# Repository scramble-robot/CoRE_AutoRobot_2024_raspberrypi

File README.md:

# SDカード

1. Raspberry Pi ImagerでRaspberry Pi OS Lite (64-bit,**bullseye**)をMicro SDに書き込む。Imagerの設定でユーザ名**pi**とパスワードを予め設定すること。
2. Micro SDに作成された"bootfs"ドライブ直下に`ssh`という名前のファイルを配置してSSHを有効化する。
3. OS起動後、本レポジトリの`ros2_ws`及び`service`ディレクトリをホームディレクトリ(`/home/pi/`)にコピーする。

# C620とのCAN通信

MCP2515を用いてSPIからCANを制御

- (参考) [RaspberryPiとMCP2515でCAN通信をやってみる](https://qiita.com/h-kiyo/items/d8583af13768ad67bcd0)

## ハードウェア
1Mbpsの通信を行うために、水晶振動子を**16MHz**に交換すること

## CAN-BUSの有効化
1. `/boot/config.txt`を編集してSPIとMCP2515を有効化する
    ```bash
    sudo vi /boot/config.txt
    ```

    ```
    # Uncomment some or all of these to enable the optional hardware interfaces
    #dtparam=i2c_arm=on
    #dtparam=i2s=on
    dtparam=spi=on

    # MCP2515
    dtparam=spi=on
    dtoverlay=mcp2515-can0,oscillator=16000000,interrupt=25
    dtoverlay=spi-bcm2835-overlay
    ```

2. 初期化できているか確認
    ```
    dmesg | grep mcp251x
    ```

## can-utilsのインストール
```bash
sudo apt install can-utils
```

## 通信テスト

1Mbpsでlink up

```bash
sudo ip link set can0 type can bitrate 1000000 loopback off
sudo ip link set can0 up
sudo ifconfig can0 txqueuelen 1000
sudo ifconfig
```

### 受信テスト
```bash
candump can0
```

C620と通信できていると、以下のようなデータが受信される。
```text
  can0  201   [8]  0E 16 00 00 FF FD 21 00
  can0  201   [8]  0E 16 00 00 FF FD 21 00
  can0  201   [8]  0E 16 00 00 FF BE 21 00
  can0  201   [8]  0E 16 00 00 FF FD 21 00
  can0  201   [8]  0E 16 00 00 00 3D 21 00
```

### 送信
モータ回るはず
```bash
cansend can0 200#0200000000000000
```

## systemdによるCANバスの自動有効化

1. systemdの設定
    ```bash
    sudo vi /etc/systemd/network/80-can.network
    ```

    ```text
    [Match]
    Name=can*

    [CAN]
    BitRate=1000000
    ```

    設定後、以下コマンド実行
    ```bash
    sudo systemctl enable systemd-networkd
    sudo systemctl start systemd-networkd
    ```

2. txqueuelenの自動設定
    ```bash
    sudo vi /etc/udev/rules.d/71-can-txqueuelen.rules
    ```

    ```
    SUBSYSTEM=="net", ACTION=="add|change", KERNEL=="can*", ATTR{tx_queue_len}="1000"
    ```

3. 再起動後、`ifconfig`でlink upしていることを確認

    ```
    can0: flags=193<UP,RUNNING,NOARP>  mtu 16
            unspec 00-00-00-00-00-00-00-00-00-00-00-00-00-00-00-00  txqueuelen 1000  (UNSPEC)
            RX packets 0  bytes 0 (0.0 B)
            RX errors 0  dropped 0  overruns 0  frame 0
            TX packets 0  bytes 0 (0.0 B)
            TX errors 0  dropped 0 overruns 0  carrier 0  collisions 0
    ```

## Pythonからの制御

```bash
pip install python-can
```

```python
import can
import struct
import time

bus = can.interface.Bus(bustype="socketcan", channel="can0", bitrate=1000000)

def set_current(bus, currents):
    d = [0]*8
    raw_array = [0]*4
    for i in range(4):
        v = int(round(currents[i]/20 * 16384))
        v = min(v, 16384)
        v = max(v, -16384)
        raw_array[i] = v
    b = struct.pack('>4h', *raw_array)
    msg = can.Message(arbitration_id=0x200, is_extended_id=False, data=b)
    bus.send(msg)

def parse_c620_data(msg: can.Message):
    data = struct.unpack('>hhhbb', msg.data)
    degree = data[0]/ 8192 * 360
    rpm = data[1]
    current = data[2]/16384*20
    temperature = data[3]
    return degree, rpm, current, temperature

def can_receive_callback(msg: can.Message) -> None:
    #print(msg)
    if msg.arbitration_id >= 0x201 and msg.arbitration_id < 0x204:
        degree, rpm, current, temperature = parse_c620_data(msg)
        print(f'{degree:.1f}\t{rpm:+5d}\t{current:.1f}\t{temperature:2d}')

notifier = can.Notifier(bus, [can_receive_callback])

set_current(bus, [1, -1, 0, 0])
time.sleep(1)

set_current(bus, [-1, 1, 0, 0])
time.sleep(1)

for i in range(4):
    set_current(bus, [0, 0, 0, 0])
    time.sleep(1)

notifier.stop()
bus.shutdown()
```

# サーボモータ
## ハードウェア
- 信号線はGPIO17に接続
- サーボモータの5Vは外部電源から取ること

## requirements
```bash
sudo apt install -y pigpio python3-pigpio
sudo pigpiod
sudo systemctl enable pigpiod
```

## 動作確認

```python
import pigpio

output_pin = 12 # 12 or 13

def setServoDegree(pi, output_pin, degree):
    min_width = 500
    max_width = 2500
    deg_range = 270
    output = degree / deg_range
    output *= max_width - min_width
    output += min_width
    output = int(output)
    pi.set_servo_pulsewidth(output_pin, output)

pi = pigpio.pi()
pi.set_mode(output_pin, pigpio.OUTPUT)
pi.set_servo_pulsewidth(output_pin, 0)

while True:
    print("input Duty Cyle (0 - 270)")
    degree = float(input())
    setServoDegree(pi, output_pin, degree)
```

# ROS2のインストール

Raspbian OS用の、[非公式のdebパッケージ](https://github.com/Ar-Ray-code/rpi-bullseye-ros2)を使ってインストールする

```bash
wget https://github.com/Ar-Ray-code/rpi-bullseye-ros2/releases/download/ros2-0.3.1/ros-humble-desktop-0.3.1_20221218_arm64.deb
sudo apt install ./ros-humble-desktop-0.3.1_20221218_arm64.deb
sudo pip install vcstool colcon-common-extensions

echo "source /opt/ros/humble/setup.bash" >> ~/.bashrc
source ~/.bashrc
```

## ROS2パッケージのビルド
```
cd ~/ros2_ws
colcon build --symlink-install
source install/local_setup.bash
echo "source ~/ros2_ws/install/setup.bash" >> ~/.bashrc
```

## ROS2ノードの実行
```bash
ros2 launch scramble_auto_robot hardware.launch.py
```
- この段階で下記のようなエラーが出る場合は，Raspberry piのOSのバージョンが誤っているためSDカード作成からやり直す必要がある．OSのバージョンはbullseyeを指定すること（何も指定しないと最新版のbookwormがインストールされる）
```[INFO] [launch]: All log files can be found below /home/pi/.ros/log/2024-02-11-18-34-23-302048-raspberrypi-2602
[INFO] [launch]: Default logging verbosity is set to INFO
[ERROR] [launch]: Caught exception in launch (see debug for traceback): Caught exception when trying to load file of format [py]: No module named 'rclpy._rclpy_pybind11'
The C extension '/opt/ros/humble/lib/python3.9/site-packages/_rclpy_pybind11.cpython-311-aarch64-linux-gnu.so' isn't present on the system. Please refer to 'https://docs.ros.org/en/humble/Guides/Installation-Troubleshooting.html#import-failing-without-library-present-on-the-system' for possible solutions
```

## 確認
```bash
ros2 topic pub /can_node/c620_0/target_current std_msgs/Float64 "{data: 1.0}"
ros2 topic pub /can_node/c620_0/target_current std_msgs/Float64 "{data: 0.0}"
ros2 topic pub /servo0/degree std_msgs/Float64 "{data: 0}"
ros2 topic pub /servo1/degree std_msgs/Float64 "{data: 0}"
ros2 topic echo /can_node/c620_0/rpm
```

## 自動起動
```bash
sudo ln -s /home/pi/service/scramble_auto_robot_ros2.service /etc/systemd/system
chmod 755 /home/pi/service/ros2_launch.sh
sudo systemctl enable scramble_auto_robot_ros2.service
sudo systemctl start scramble_auto_robot_ros2.service
systemctl status scramble_auto_robot_ros2.service
```

# 起動オプションの変更
1. ターミナルで`sudo raspi-config`を実行
2. "1. System Options"を選択
3. "S6 Network as Boot"でネットワーク確率までBootを待つように設定
4. "S5 Boot / Auto Login"で"Console Autologin"を選択

# SDカードのRead only化
SDカードへの書き込み中に電源を抜くとSDカードが壊れる可能性があるので、read-onlyに設定する。

参考: [Raspberry Pi で Overlay File System (read-only file system) を試す](https://qiita.com/nanbuwks/items/d5d0cfc5f94177515a6a)

1. ターミナルで`sudo raspi-config`を実行
2. "4 Performance Options Configure performance settings"
3. "P3 Overlay File System Enable/disable read-only file system"
4. 有効化して再起動

# その他
- ros2_launch.shにて`ROS_DOMAIN_ID=0`に設定しています。
- デフォルトの設定ではIPアドレスの割当はDHCPで行われます。

# Third-party license
本手順で作成した場合、以下のサードパーティ製ソフトウェアがインストールされます。
(本レポジトリに直接は含まれていません)

- Raspbian OS
- ROS2 Humble
- [rpi-bullseye-ros2](https://github.com/Ar-Ray-code/rpi-bullseye-ros2/blob/main/LICENSE) (MIT License)
- [python-can](https://pypi.org/project/python-can/) (LGPL v3)
- [pigpio](https://github.com/joan2937/pigpio/blob/master/UNLICENCE) (Unlicense)

デバッグ用
- [can-utils](https://github.com/linux-can/can-utils/tree/master/LICENSES)

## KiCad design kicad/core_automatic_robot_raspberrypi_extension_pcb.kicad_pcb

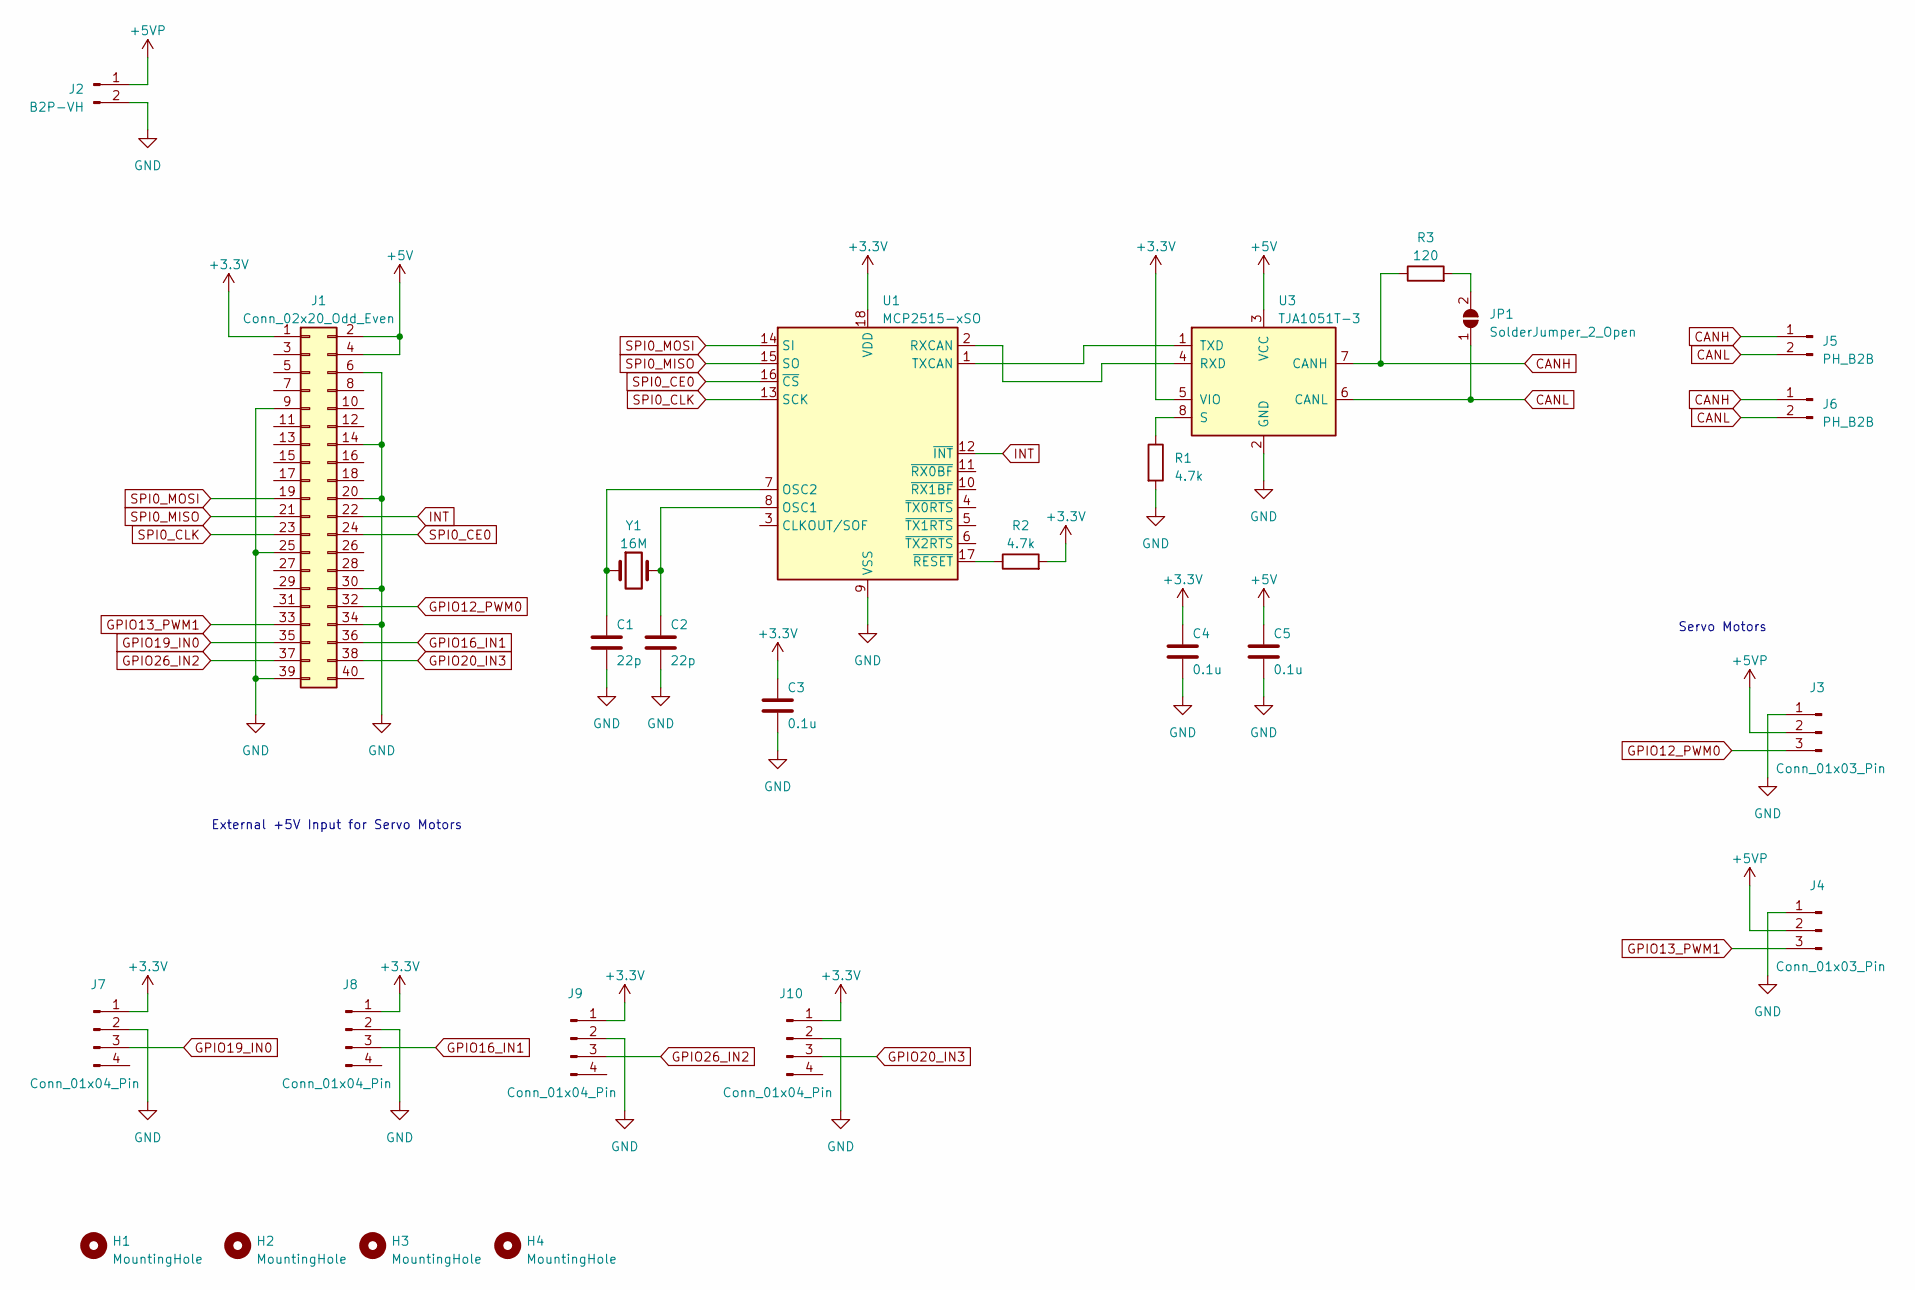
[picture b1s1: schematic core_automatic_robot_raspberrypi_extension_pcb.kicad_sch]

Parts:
C1, C2: 22p; C_0603_1608Metric_Pad1.08x0.95mm_HandSolder
C3, C4, C5: 0.1u; C_0603_1608Metric_Pad1.08x0.95mm_HandSolder
H1, H2, H3, H4: MountingHole; MountingHole_3.2mm_M3
J1: Conn_02x20_Odd_Even; PinHeader_2x20_P2.54mm_Vertical
J2: B2P-VH; JST_VH_B2P-VH-B_1x02_P3.96mm_Vertical
J3, J4: Conn_01x03_Pin; PinHeader_1x03_P2.54mm_Horizontal
J5, J6: PH_B2B; JST_PH_B2B-PH-K_1x02_P2.00mm_Vertical
J7, J8, J9, J10: Conn_01x04_Pin; JST_XH_B4B-XH-A_1x04_P2.50mm_Vertical
JP1: SolderJumper_2_Open; SolderJumper-2_P1.3mm_Open_Pad1.0x1.5mm
R1, R2: 4.7k; R_0603_1608Metric_Pad0.98x0.95mm_HandSolder
R3: 120; R_0603_1608Metric_Pad0.98x0.95mm_HandSolder
U1: MCP2515-xSO; SOIC-18W_7.5x11.6mm_P1.27mm
U3: TJA1051T-3; SOIC-8_3.9x4.9mm_P1.27mm
Y1: 16M; Crystal_HC49-U_Vertical

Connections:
+3.3V: C3.1, C4.1, J1.1, J7.1, J8.1, J9.1, J10.1, R2.2, U1.18 (VDD), U3.5 (VIO)
+5V: C5.1, J1.2, J1.4, U3.3 (VCC)
+5VP: J2.1, J3.2, J4.2
CANH: J5.1, J6.1, R3.1, U3.7 (CANH)
CANL: J5.2, J6.2, JP1.1 (A), U3.6 (CANL)
GND: C1.2, C2.2, C3.2, C4.2, C5.2, J1.6, J1.9, J1.14, J1.20, J1.25, J1.30, J1.34, J1.39, J2.2, J3.1, J4.1, J7.2, J8.2, J9.2, J10.2, R1.2, U1.9 (VSS), U3.2 (GND)
GPIO12_PWM0: J1.32, J3.3
GPIO13_PWM1: J1.33, J4.3
GPIO16_IN1: J1.36, J8.3
GPIO19_IN0: J1.35, J7.3
GPIO20_IN3: J1.38, J10.3
GPIO26_IN2: J1.37, J9.3
INT: J1.22, U1.12 (~INT)
unnamed: JP1.2 (B), R3.2
unnamed: C2.1, U1.8 (OSC1), Y1.2
unnamed: C1.1, U1.7 (OSC2), Y1.1
unnamed: U1.2 (RXCAN), U3.4 (RXD)
unnamed: U1.1 (TXCAN), U3.1 (TXD)
unnamed: R2.1, U1.17 (~RESET)
unnamed: R1.1, U3.8 (S)
SPI0_CE0: J1.24, U1.16 (~CS)
SPI0_CLK: J1.23, U1.13 (SCK)
SPI0_MISO: J1.21, U1.15 (SO)
SPI0_MOSI: J1.19, U1.14 (SI)

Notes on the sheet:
Servo Motors
External +5V Input for Servo Motors

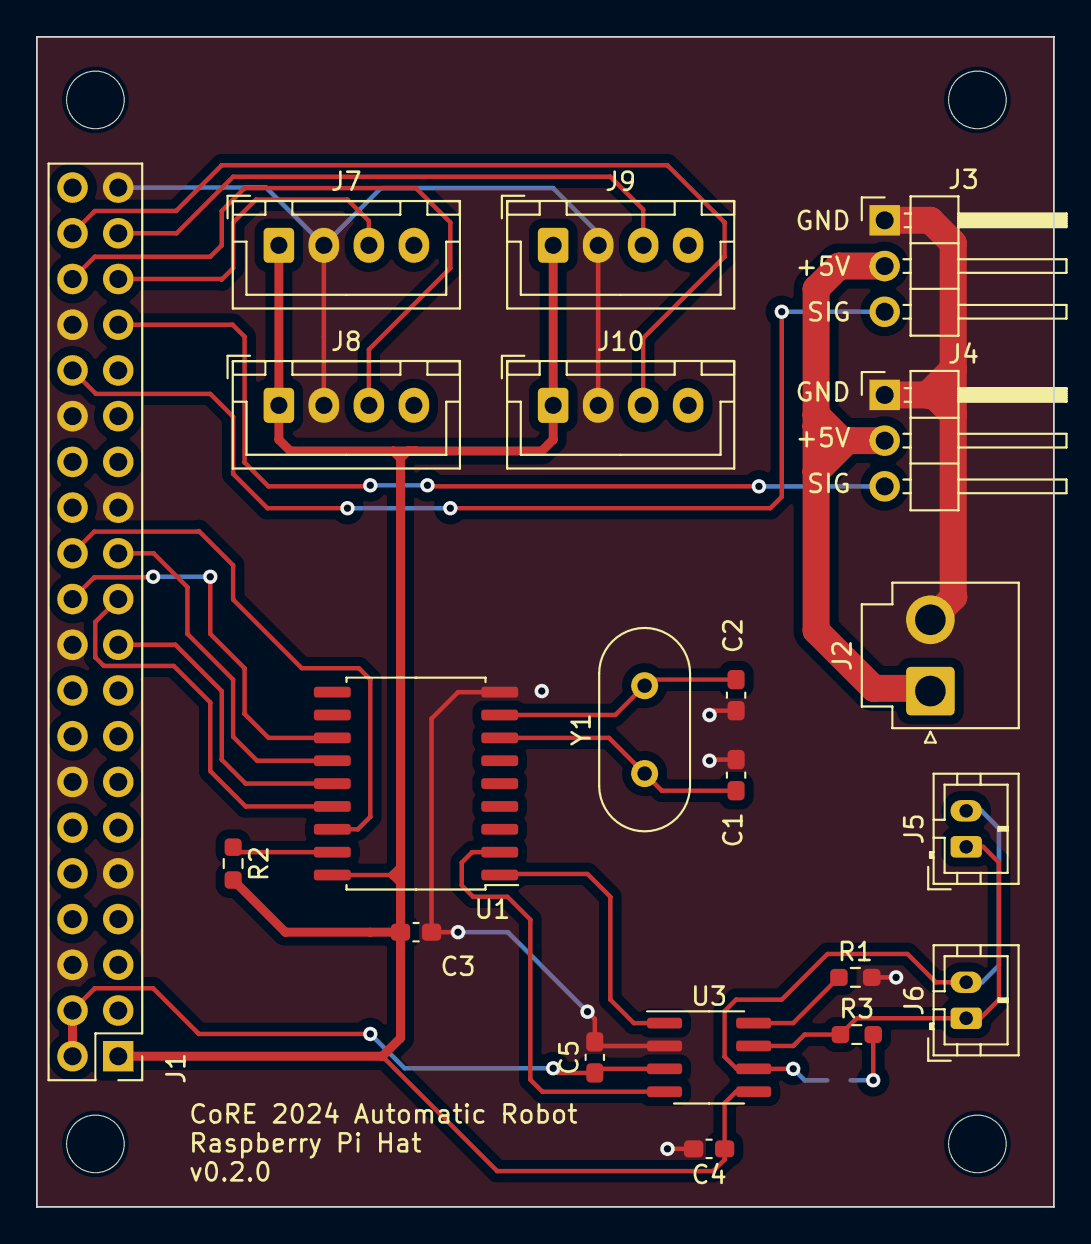
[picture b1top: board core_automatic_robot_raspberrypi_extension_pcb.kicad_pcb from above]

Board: 2 copper layers, 56.5 x 65.0 mm, 26 parts (1 on the bottom side), 24 nets.

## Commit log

2025-01-07 ROS 2ノード実行時のエラーに関するトラブルシューティングを追加
2025-01-21 ROS 2ノード自動起動がうまくいかない問題に対する修正
2025-01-21 フォトインタラプタが反応してもモータが止まらない問題を修正
2025-03-07 動作確認スクリプトのpwm指定が間違っている件の修正
